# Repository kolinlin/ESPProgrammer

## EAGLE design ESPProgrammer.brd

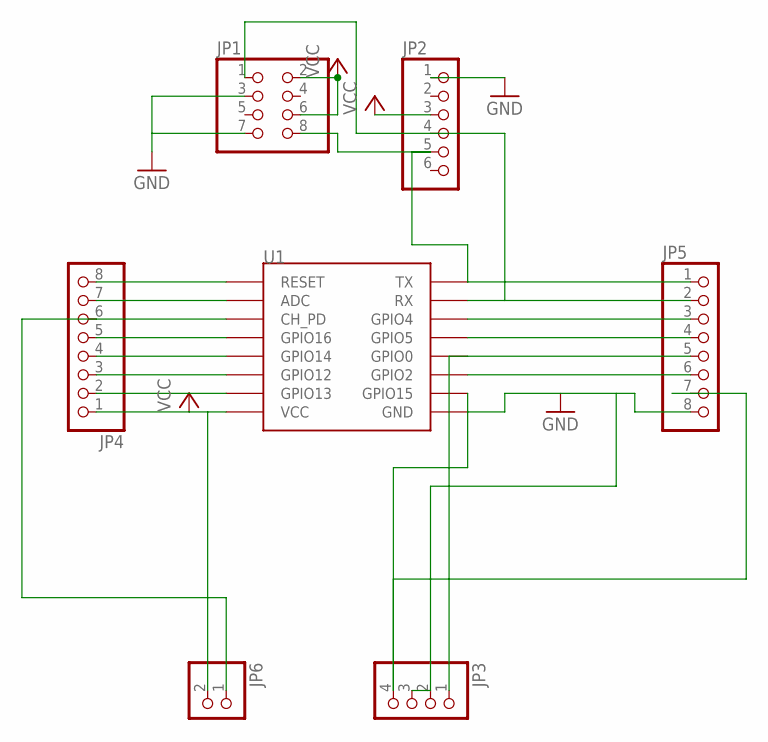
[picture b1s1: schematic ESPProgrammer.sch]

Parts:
JP1: PINHD-2X4; 2X04
JP2: PINHD-1X6; 1X06
JP3: PINHD-1X4; 1X04
JP4, JP5: PINHD-1X8; 1X08
JP6: PINHD-1X2; 1X02
U1: ESP12

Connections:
GND: JP1.3, JP1.7, JP2.1, JP3.2, JP3.3, JP5.8, U1.GND
unnamed: JP3.1, JP5.5, U1.GPIO0
unnamed: JP3.4, JP5.7, U1.GPIO15
unnamed: JP5.3, U1.GPIO4
unnamed: JP1.1, JP2.4, JP5.2, U1.RX
unnamed: JP1.8, JP2.5, JP5.1, U1.TX
unnamed: JP5.4, U1.GPIO5
unnamed: JP5.6, U1.GPIO2
unnamed: JP4.8, U1.RESET
unnamed: JP4.7, U1.ADC
unnamed: JP4.5, U1.GPIO16
unnamed: JP4.4, U1.GPIO14
unnamed: JP4.3, U1.GPIO12
unnamed: JP4.2, U1.GPIO13
unnamed: JP4.6, JP6.1, U1.CH_PD
VCC: JP1.2, JP1.6, JP2.3, JP4.1, JP6.2, U1.VCC

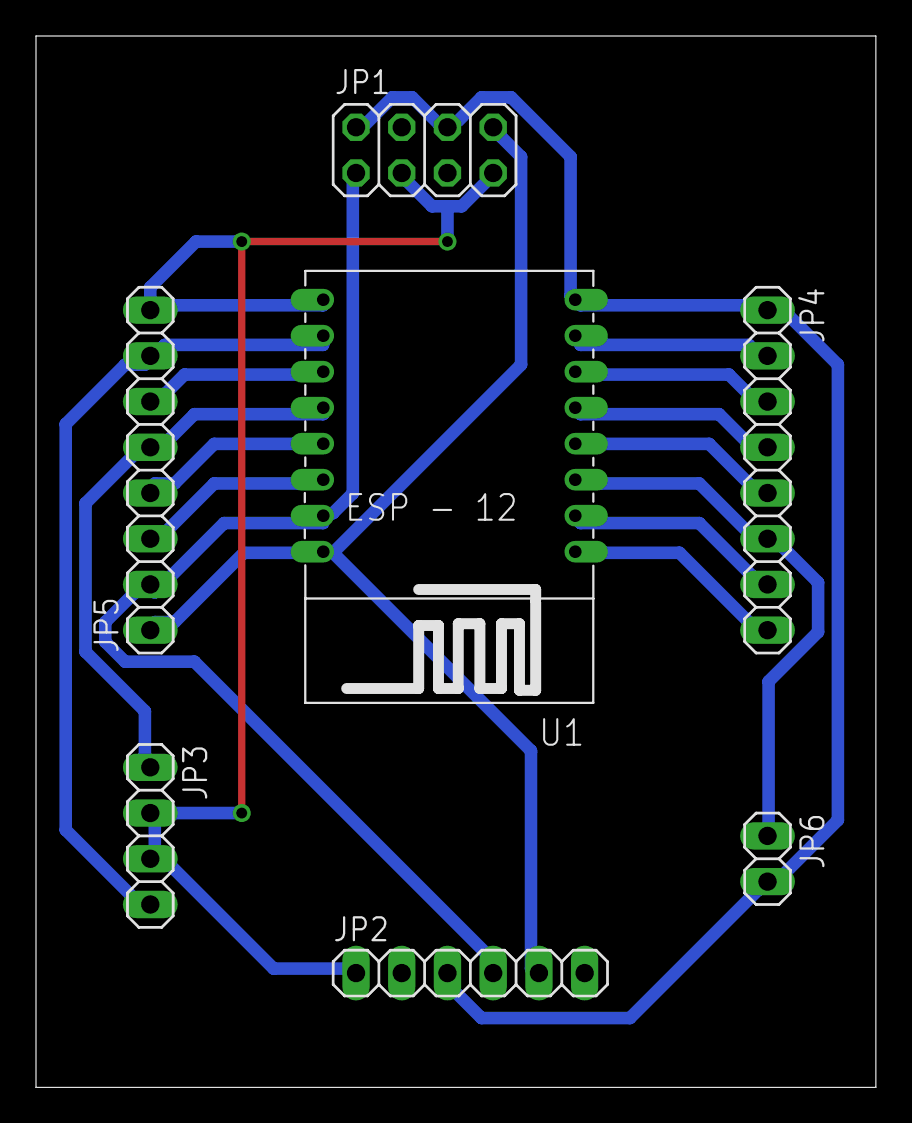
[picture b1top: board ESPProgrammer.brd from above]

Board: 2 copper layers, 46.7 x 58.4 mm, 7 parts (0 on the bottom side), 16 nets.

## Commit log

2017-02-28 init project
2017-02-28 add eagle file
2017-02-28 update file
